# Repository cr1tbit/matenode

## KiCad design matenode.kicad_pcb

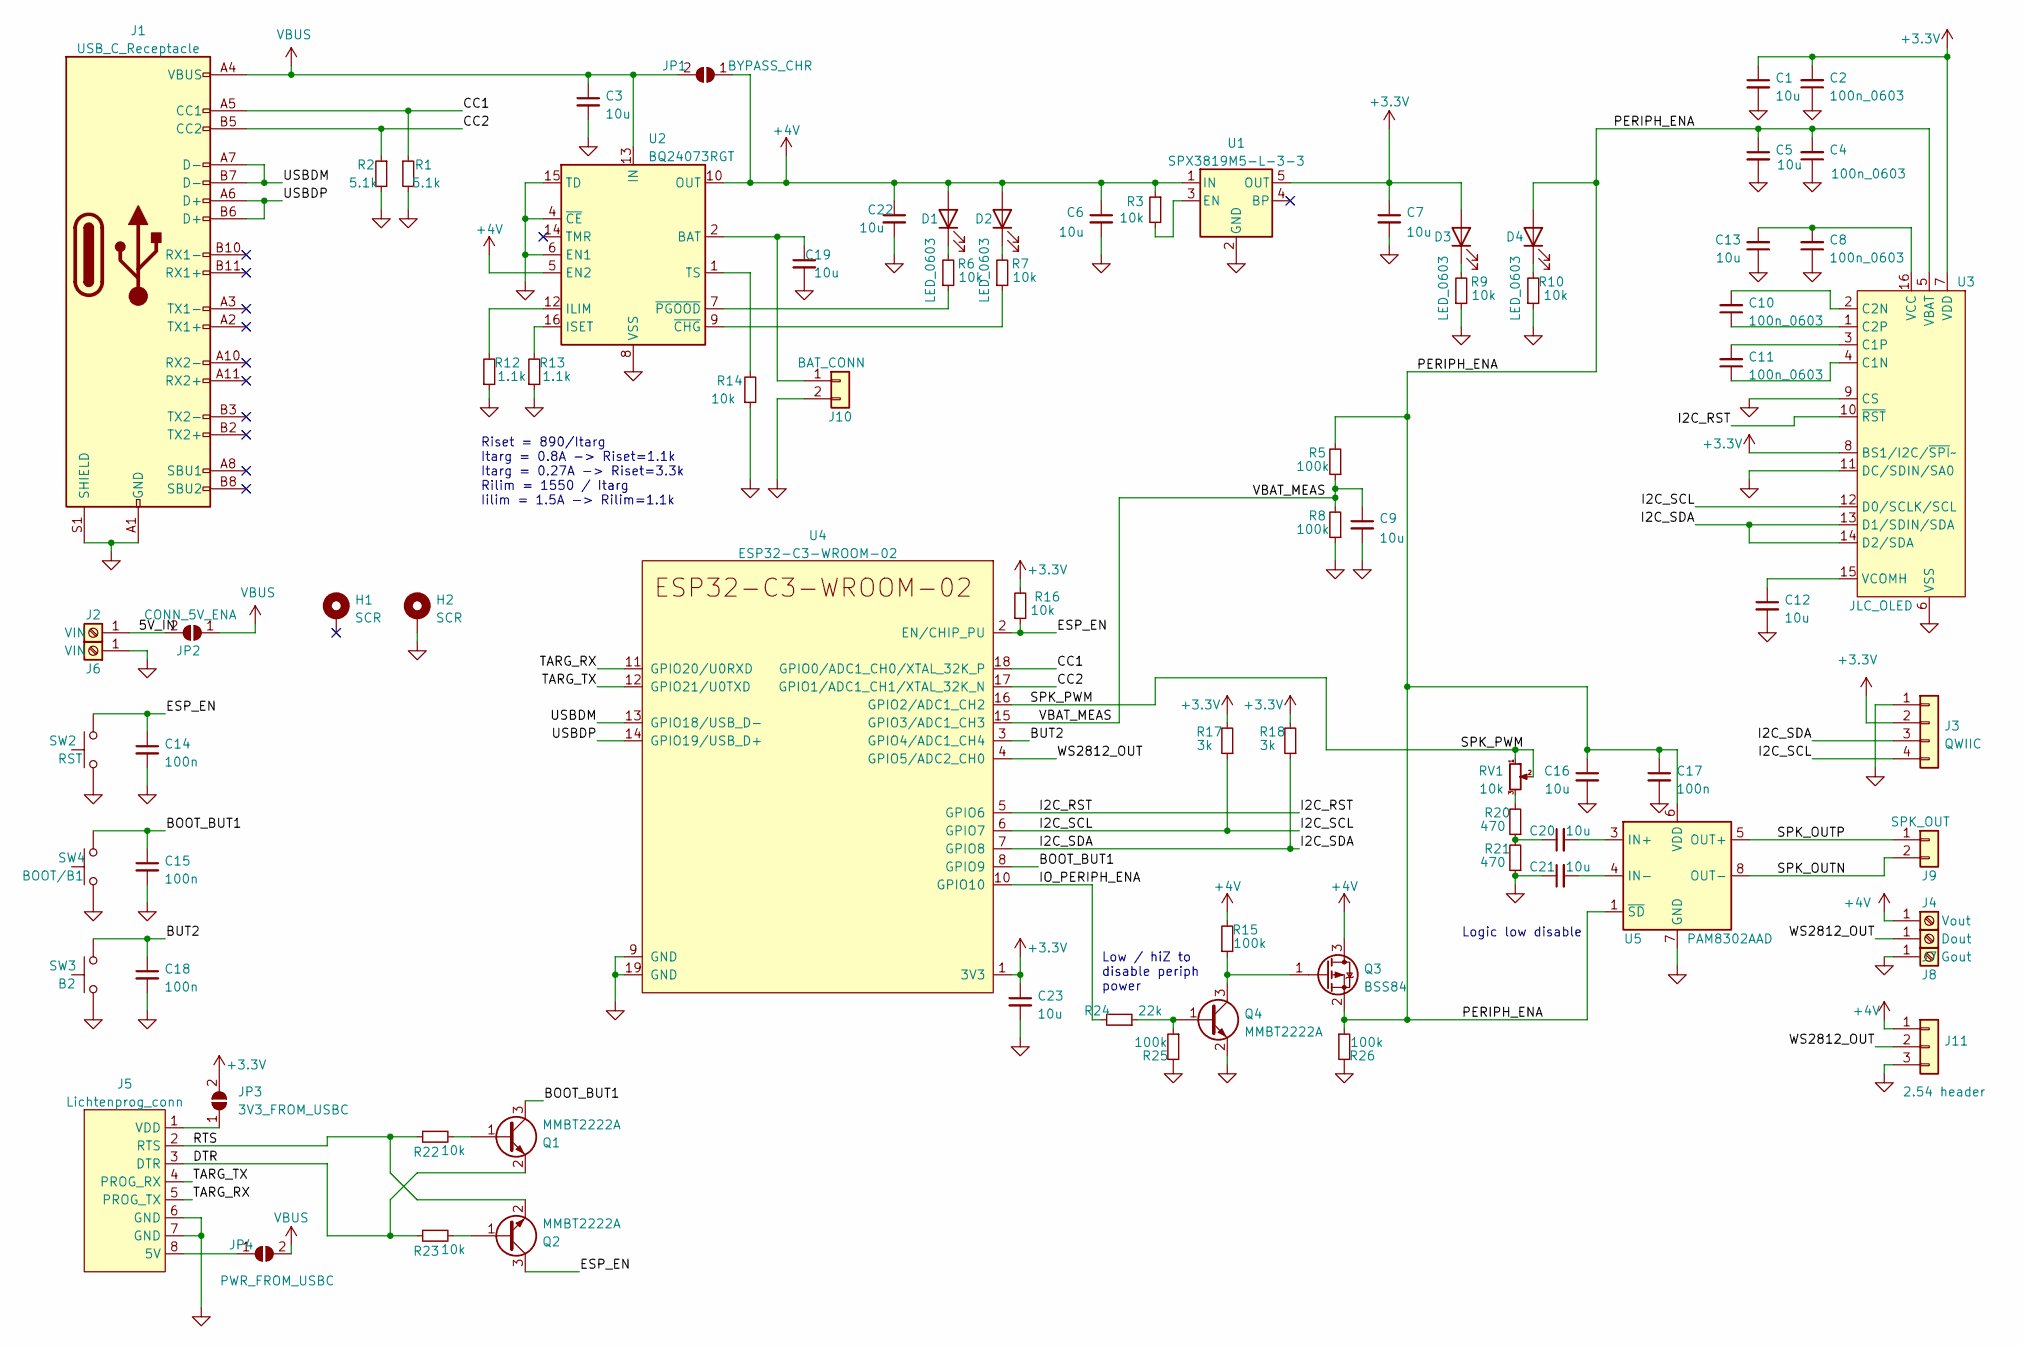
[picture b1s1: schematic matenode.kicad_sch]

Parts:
C1, C5, C12, C13, C16, C20, C21, C23: 10u; C_0402_1005Metric
C2, C4, C8, C10, C11: 100n_0603; C_0603_1608Metric_Pad1.08x0.95mm_HandSolder
C3, C6, C7, C9, C19, C22: 10u; C_0402_1005Metric; LCSC C19702
C14, C15, C17, C18: 100n; C_0402_1005Metric
D1, D2, D3, D4: LED_0603; LED_0603_1608Metric_Pad1.05x0.95mm_HandSolder
H1, H2: SCR; MountingHole_3.2mm_M3_ISO7380_Pad
J1: USB_C_Receptacle; USB_C_Receptacle_HRO_TYPE-C-31-M-12
J2, J6: VIN; DG235-5.0
J3: QWIIC; JST_SH_SM04B-SRSS-TB_1x04-1MP_P1.00mm_Horizontal
J4: Vout; DG235-5.0
J5: Lichtenprog_conn; Lichtenprog
J7: Dout; DG235-5.0
J8: Gout; DG235-5.0
J9: SPK_OUT; JST_PH_S2B-PH-K_1x02_P2.00mm_Horizontal
J10: BAT_CONN; JST_PH_S2B-PH-K_1x02_P2.00mm_Horizontal
J11: 2.54 header; PinHeader_1x03_P2.54mm_Vertical
JP1: BYPASS_CHR; SolderJumper-2_P1.3mm_Open_TrianglePad1.0x1.5mm
JP2: CONN_5V_ENA; SolderJumper-2_P1.3mm_Open_TrianglePad1.0x1.5mm
JP3: 3V3_FROM_USBC; SolderJumper-2_P1.3mm_Open_TrianglePad1.0x1.5mm
JP4: PWR_FROM_USBC; SolderJumper-2_P1.3mm_Open_TrianglePad1.0x1.5mm
Q1, Q2, Q4: MMBT2222A; SOT-23
Q3: BSS84; SOT-23
R1, R2: 5.1k; R_0402_1005Metric; LCSC C25117
R3: 10k; R_0402_1005Metric; LCSC C25768
R5, R8, R15, R25, R26: 100k; R_0402_1005Metric; LCSC C25117
R6, R7, R9, R10, R16, R22, R23: 10k; R_0402_1005Metric; LCSC C25117
R12, R13: 1.1k; R_0603_1608Metric; LCSC C25117
R14: 10k; R_0603_1608Metric; LCSC C25768
R17, R18: 3k; R_0402_1005Metric; LCSC C25117
R20, R21: 470; R_0402_1005Metric; LCSC C25117
R24: 22k; R_0402_1005Metric; LCSC C25768
RV1: 10k; Potentiometer_Bourns_TC33X_Vertical
SW2: RST; SW_SPST_FSMSM
SW3: B2; SW_SPST_TL3342
SW4: BOOT/B1; SW_SPST_TL3342
U1: SPX3819M5-L-3-3; SOT-23-5
U2: BQ24073RGT; VQFN-16-1EP_3x3mm_P0.5mm_EP1.6x1.6mm_ThermalVias
U3: JLC_OLED; OLED-042-JLC
U4: ESP32-C3-WROOM-02
U5: PAM8302AAD; MSOP-8_3x3mm_P0.65mm

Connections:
+3.3V: C1.1, C2.2, C7.1, C23.1, D3.2 (A), J3.2, JP3.2 (B), R16.2, R17.2, R18.2, U1.5 (OUT), U3.7 (VDD), U3.8 (BS1/I2C/~SPI~), U4.1 (3V3)
+4V: C6.1, C22.1, D1.2 (A), D2.2 (A), J4.1, J11.1, JP1.1 (A), Q3.3 (D), R3.1, R15.2, U1.1 (IN), U2.5 (EN2), U2.10 (OUT), U2.11 (OUT)
/5V_IN: J2.1, JP2.2 (B)
/BOOT_BUT1: C15.1, Q1.3 (C), SW4.2, U4.8 (GPIO9)
/BUT2: C18.1, SW3.2, U4.3 (GPIO4/ADC1_CH4)
/CC1: J1.A5 (CC1), R1.1, U4.18 (GPIO0/ADC1_CH0/XTAL_32K_P)
/CC2: J1.B5 (CC2), R2.1, U4.17 (GPIO1/ADC1_CH1/XTAL_32K_N)
/DTR: J5.3 (DTR), Q1.2 (E), R23.1
/ESP_EN: C14.1, Q2.3 (C), R16.1, SW2.2, U4.2 (EN/CHIP_PU)
/I2C_RST: U3.10 (~RST), U4.5 (GPIO6)
/I2C_SCL: J3.4, R17.1, U3.12 (D0/SCLK/SCL), U4.6 (GPIO7)
/I2C_SDA: J3.3, R18.1, U3.13 (D1/SDIN/SDA), U3.14 (D2/SDA), U4.7 (GPIO8)
/IO_PERIPH_ENA: R24.2, U4.10 (GPIO10)
/PERIPH_ENA: C4.2, C5.1, C16.1, C17.1, D4.2 (A), Q3.2 (S), R5.2, R26.1, U3.5 (VBAT), U5.1 (~SD), U5.6 (VDD)
/RTS: J5.2 (RTS), Q2.2 (E), R22.1
/SPK_OUTN: J9.2, U5.8 (OUT-)
/SPK_OUTP: J9.1, U5.5 (OUT+)
/SPK_PWM: RV1.1, RV1.2, U4.16 (GPIO2/ADC1_CH2)
/TARG_RX: J5.5 (PROG_TX), U4.11 (GPIO20/U0RXD)
/TARG_TX: J5.4 (PROG_RX), U4.12 (GPIO21/U0TXD)
/USBDM: J1.A7 (D-), J1.B7 (D-), U4.13 (GPIO18/USB_D-)
/USBDP: J1.A6 (D+), J1.B6 (D+), U4.14 (GPIO19/USB_D+)
/VBAT_MEAS: C9.1, R5.1, R8.2, U4.15 (GPIO3/ADC1_CH3)
/WS2812_OUT: J7.1, J11.2, U4.4 (GPIO5/ADC2_CH0)
GND: C1.2, C2.1, C3.2, C4.1, C5.2, C6.2, C7.2, C8.1, C9.2, C12.2, C13.1, C14.2, C15.2, C16.2, C17.2, C18.2, C19.2, C21.1, C22.2, C23.2, H2.1, J1.A1 (GND), J1.A12 (GND), J1.B1 (GND), J1.B12 (GND), J1.S1 (SHIELD), J3.1, J5.6 (GND), J5.7 (GND), J6.1, J8.1, J10.2, J11.3, Q4.2 (E), R1.2, R2.2, R8.1, R9.1, R10.1, R12.1, R13.1, R14.1, R21.1, R25.2, R26.2, SW2.1, SW3.1, SW4.1, U1.2 (GND), U2.4 (~CE), U2.6 (EN1), U2.8 (VSS), U2.15 (TD), U2.17 (VSS), U3.6 (VSS), U3.9 (CS), U3.11 (DC/SDIN/SA0), U4.9 (GND), U4.19 (GND), U5.7 (GND)
unnamed: C10.1, U3.1 (C2P)
unnamed: C10.2, U3.2 (C2N)
unnamed: C11.1, U3.4 (C1N)
unnamed: C11.2, U3.3 (C1P)
unnamed: C12.1, U3.15 (VCOMH)
unnamed: C8.2, C13.2, U3.16 (VCC)
unnamed: C19.1, J10.1, U2.2 (BAT), U2.3 (BAT)
unnamed: C20.1, R20.1, R21.2
unnamed: C20.2, U5.3 (IN+)
unnamed: C21.2, U5.4 (IN-)
unnamed: D1.1 (K), R6.2
unnamed: D2.1 (K), R7.2
unnamed: D3.1 (K), R9.2
unnamed: D4.1 (K), R10.2
unnamed: J5.1 (VDD), JP3.1 (A)
unnamed: J5.8 (5V), JP4.1 (A)
unnamed: Q1.1 (B), R22.2
unnamed: Q2.1 (B), R23.2
unnamed: Q3.1 (G), Q4.3 (C), R15.1
unnamed: Q4.1 (B), R24.1, R25.1
unnamed: R3.2, U1.3 (EN)
unnamed: R6.1, U2.7 (~PGOOD)
unnamed: R7.1, U2.9 (~CHG)
unnamed: R12.2, U2.12 (ILIM)
unnamed: R13.2, U2.16 (ISET)
unnamed: R14.2, U2.1 (TS)
unnamed: R20.2, RV1.3
VBUS: C3.1, J1.A4 (VBUS), J1.A9 (VBUS), J1.B4 (VBUS), J1.B9 (VBUS), JP1.2 (B), JP2.1 (A), JP4.2 (B), U2.13 (IN)

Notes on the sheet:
Logic low disable
Riset = 890/Itarg Itarg = 0.8A -> Riset=1.1k Itarg = 0.27A -> Riset=3.3k Rilim = 1550 / Itarg Iilim = 1.5A -> Rilim=1.1k
Low / hiZ to disable periph power

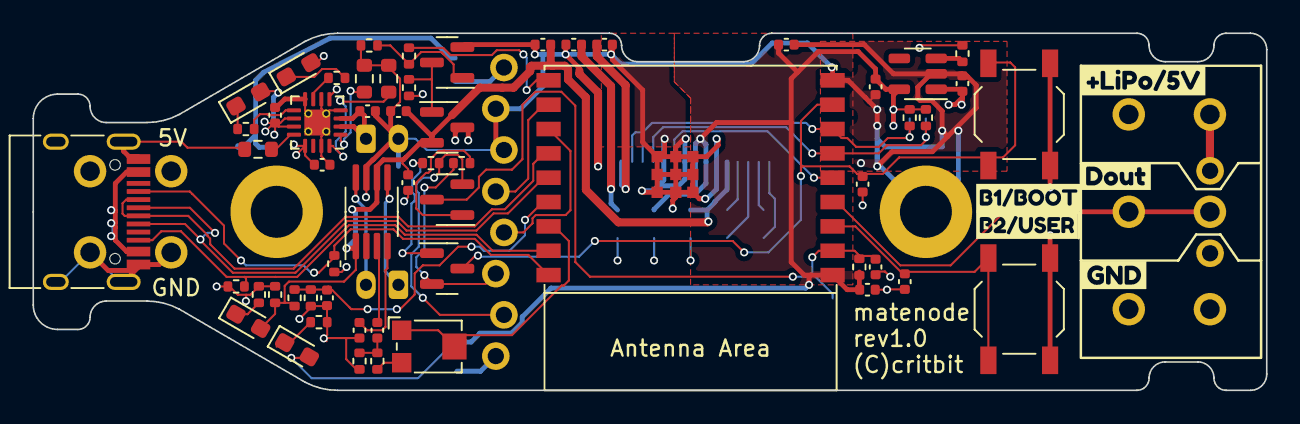
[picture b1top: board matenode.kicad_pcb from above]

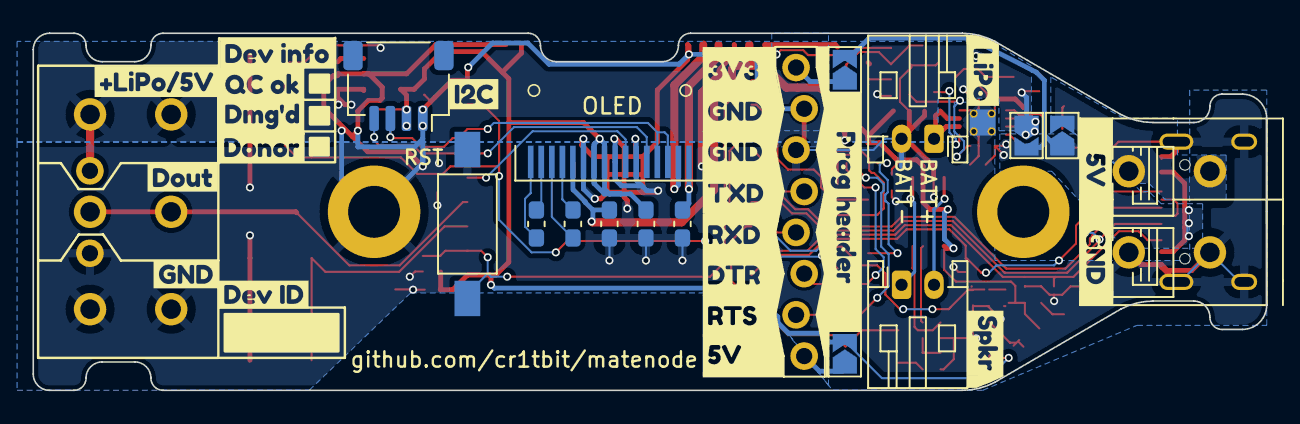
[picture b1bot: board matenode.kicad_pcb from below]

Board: 2 copper layers, 76.0 x 22.0 mm, 107 parts (39 on the bottom side), 53 nets.

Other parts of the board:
kibuzzard-6394BD6B, kibuzzard-6394BD6B#2: G***; kibuzzard-6394BD6B
kibuzzard-6394BE40: G***; kibuzzard-6394BE40
kibuzzard-6394BE58: G***; kibuzzard-6394BE58
kibuzzard-6394BED6: G***; kibuzzard-6394BED6
kibuzzard-6394BEEF: G***; kibuzzard-6394BEEF
kibuzzard-6394BF0B: G***; kibuzzard-6394BF0B
kibuzzard-6394BF19: G***; kibuzzard-6394BF19
kibuzzard-6394C0D2: G***; kibuzzard-6394C0D2
kibuzzard-6394C6B5: G***; kibuzzard-6394C6B5
kibuzzard-6394C6E9: G***; kibuzzard-6394C6E9
kibuzzard-6394C46A: G***; kibuzzard-6394C46A
kibuzzard-6394C47E: G***; kibuzzard-6394C47E
kibuzzard-6394C108: G***; kibuzzard-6394C108
kibuzzard-6394C173: G***; kibuzzard-6394C173
kibuzzard-6394C273: G***; kibuzzard-6394C273
kibuzzard-6394C445: G***; kibuzzard-6394C445
kibuzzard-6394C560: G***; kibuzzard-6394C560
kibuzzard-6394C922: G***; kibuzzard-6394C922
kibuzzard-6394C938: G***; kibuzzard-6394C938
kibuzzard-6394CBE8, kibuzzard-6394CBE8#2: G***; kibuzzard-6394CBE8
kibuzzard-6394CC15, kibuzzard-6394CC15#2: G***; kibuzzard-6394CC15
kibuzzard-6394D7BF: G***; kibuzzard-6394D7BF
kibuzzard-63966DAE, kibuzzard-63966DAE#2: G***; kibuzzard-63966DAE

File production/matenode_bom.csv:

Comment,Designator,Footprint,LCSC,mouser,MPN,MANU,checked
10u,"C1,C3,C5,C6,C7,C9,C12,C13,C16,C19,C20,C21,C22,C23",Capacitor_SMD:C_0402_1005Metric,,,,,
100n,"C14,C15,C17,C18",Capacitor_SMD:C_0402_1005Metric,,,,,
LED_0603,"D1,D2,D3,D4",LED_SMD:LED_0603_1608Metric_Pad1.05x0.95mm_HandSolder,,,,,
USB_C_Receptacle,J1,Connector_USB:USB_C_Receptacle_HRO_TYPE-C-31-M-12,,,,,
MMBT2222A,"Q1,Q2,Q4",Package_TO_SOT_SMD:SOT-23,,,,,
BSS84,Q3,Package_TO_SOT_SMD:SOT-23,,,,,
5.1k,"R1,R2",Resistor_SMD:R_0402_1005Metric,,,,,
1.1k,"R12,R13",Resistor_SMD:R_0402_1005Metric,,,,,
3k,"R17,R18",Resistor_SMD:R_0402_1005Metric,,,,,
470,"R20,R21",Resistor_SMD:R_0402_1005Metric,,,,,
22k,R24,Resistor_SMD:R_0402_1005Metric,,,,,
10k,"R3,R6,R7,R9,R10,R14,R16,R22,R23",Resistor_SMD:R_0402_1005Metric,,,,,
100k,"R5,R8,R15,R25,R26",Resistor_SMD:R_0402_1005Metric,,,,,
10k,RV1,Potentiometer_SMD:Potentiometer_Bourns_TC33X_Vertical,,,,,
B2,SW3,Button_Switch_SMD:SW_SPST_TL3342,,,,,
BOOT/B1,SW4,Button_Switch_SMD:SW_SPST_TL3342,,,,,
SPX3819M5-L-3-3,U1,Package_TO_SOT_SMD:SOT-23-5,,,,,
BQ24073RGT,U2,Package_DFN_QFN:VQFN-16-1EP_3x3mm_P0.5mm_EP1.6x1.6mm_ThermalVias,,,,,
ESP32-C3-WROOM-02,U4,Espressif:ESP32-C3-WROOM-02,,,,,
PAM8302AAD,U5,Package_SO:MSOP-8_3x3mm_P0.65mm,,,,,

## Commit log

2022-12-10 add project files
2022-12-10 finish routing. Now for aesthetics..
2022-12-10 finish silk, add prod files
2022-12-10 add schematic
2022-12-10 cleanup schematic
2022-12-12 final final
2024-05-28 start rework
